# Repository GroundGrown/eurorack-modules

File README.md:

# eurorack-modules
All my older eurorack module designs

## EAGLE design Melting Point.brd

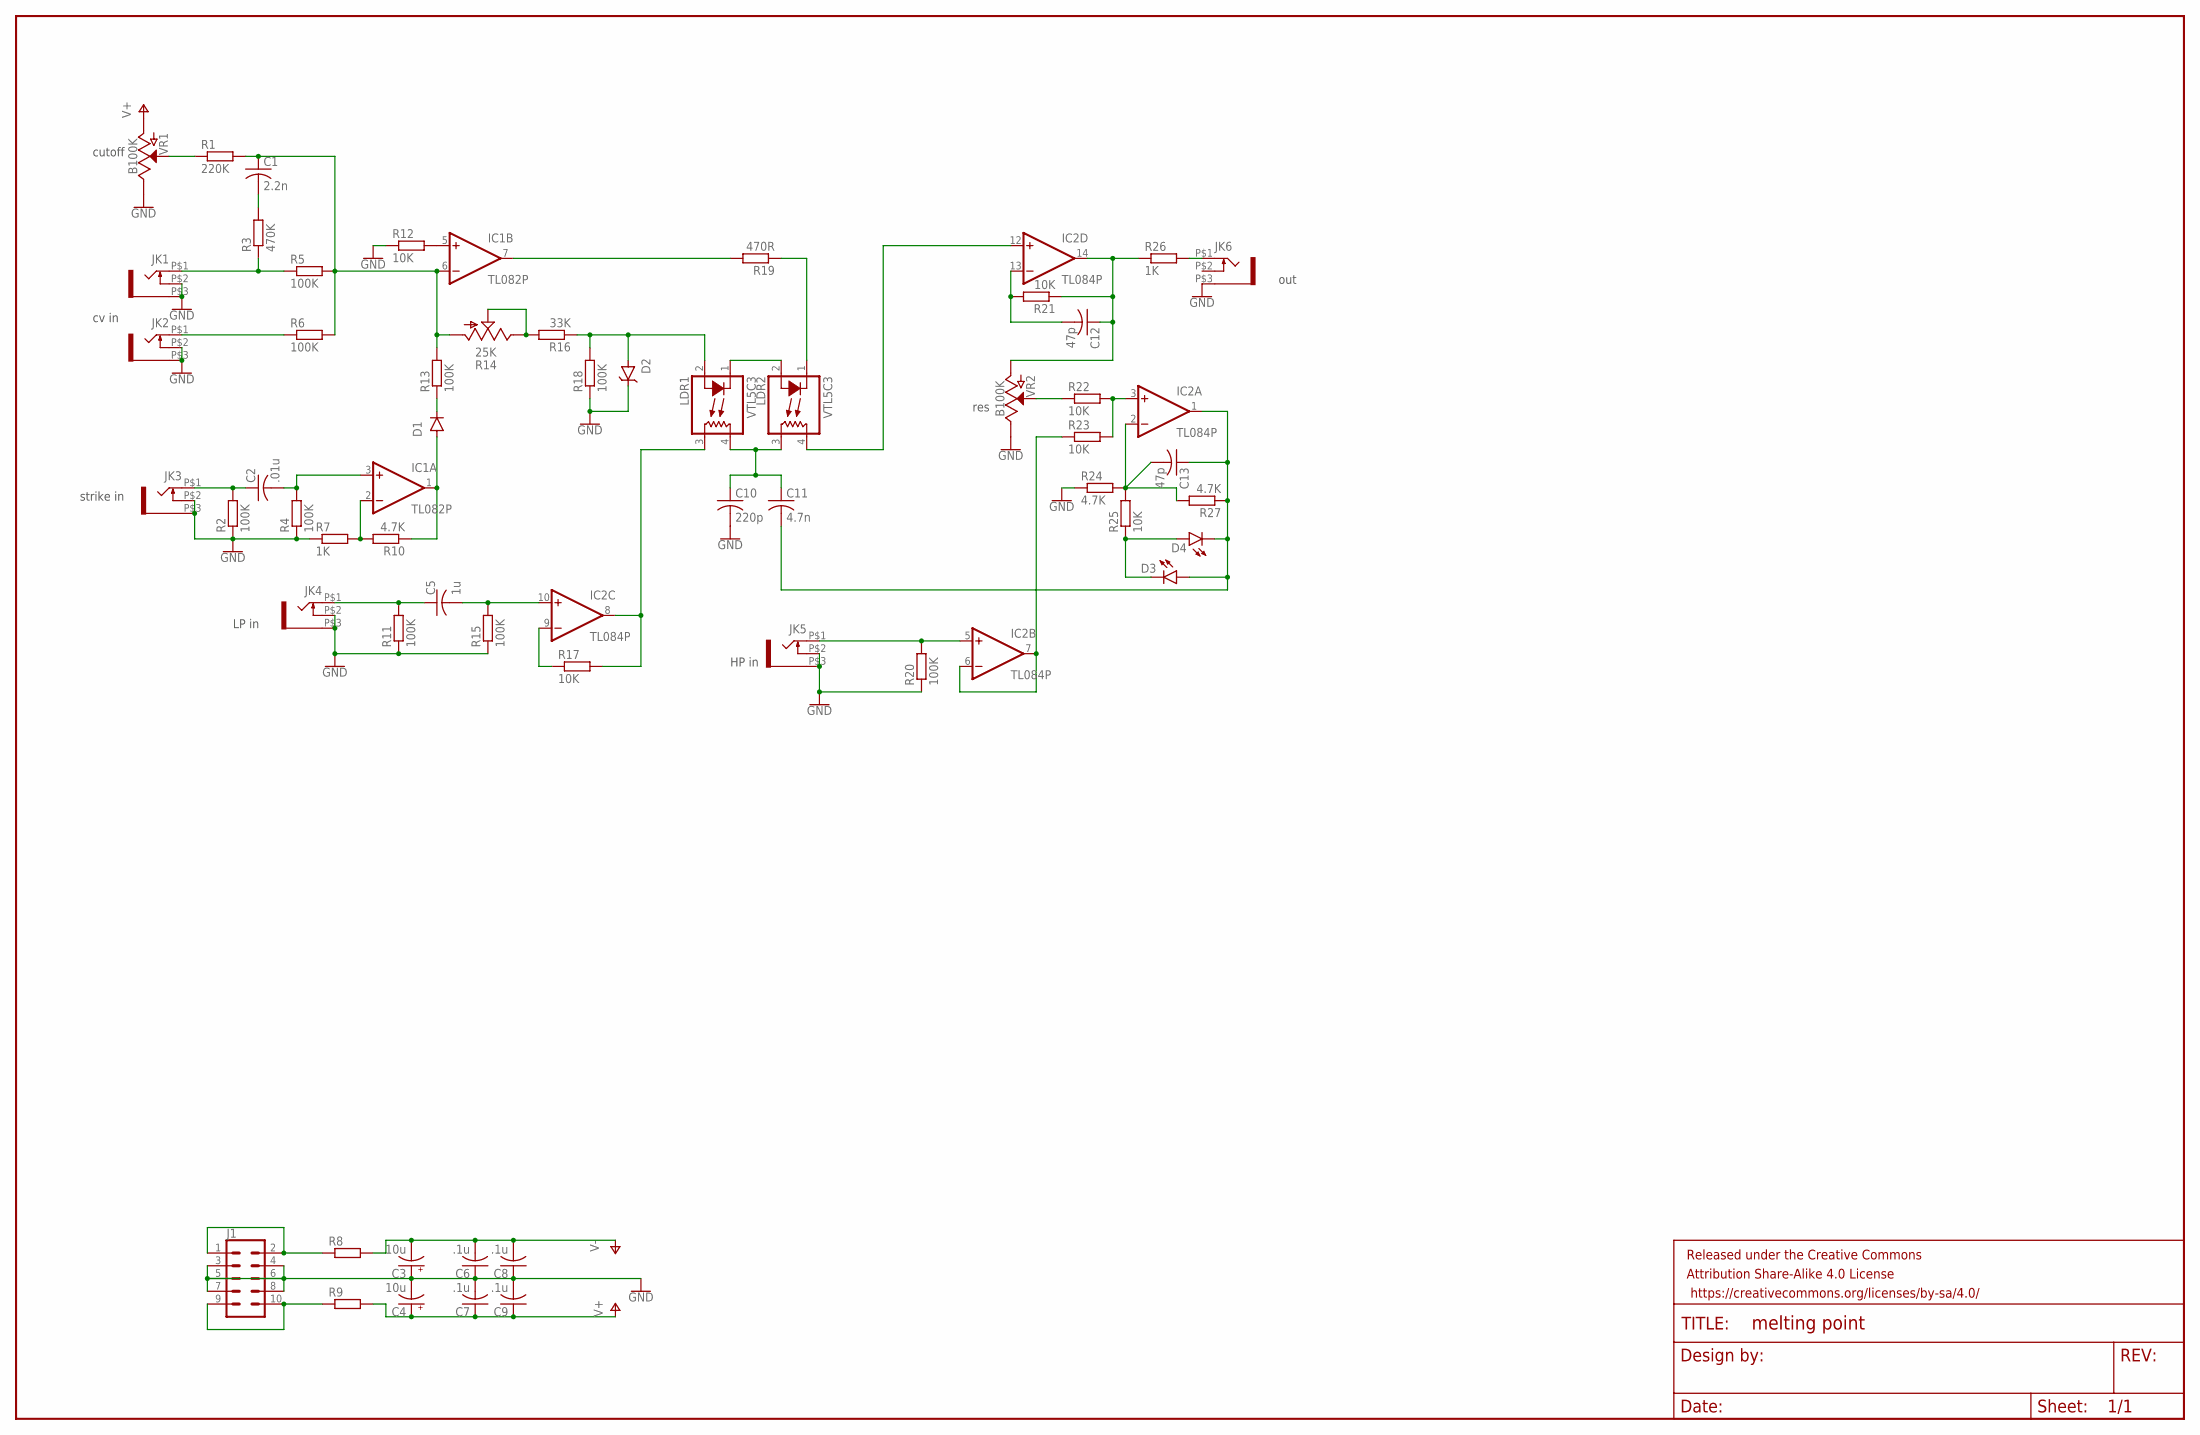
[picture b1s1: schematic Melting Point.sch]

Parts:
C1: 2.2n; C025-025X050
C2: .01u; C025-025X050
C3, C4: 10u; E2,5-6
C5: 1u; C050-045X075
C6, C7, C8, C9: .1u; C025-025X050
C10: 220p; C050-025X075
C11: 4.7n; C050-025X075
C12, C13: 47p; C025-025X050
D1: 1N4148DO35-7; DO35-7
D2: 1N4732A-TAP; DO-41
D3, D4: LED3MM; LED_3MM
FRAME1: FRAME-LEDGERNO_FOOTPRINT; DUMMY
IC1: TL082P; DIL08
IC2: TL084P; DIL14
J1: CONN_05X2PTH; 2X5
JK1, JK2, JK3, JK4, JK5, JK6: WQP-PJ301M-12_JACK
LDR1, LDR2: VTL5C3; VTL5C
R1: 220K; 0207/10
R2, R4, R5, R6, R11, R13, R15, R18, R20: 100K; 0207/10
R3: 470K; 0207/10
R7, R26: 1K; 0207/10
R8, R9: R-EU_0207/10; 0207/10
R10, R24, R27: 4.7K; 0207/10
R12, R17, R21, R22, R23, R25: 10K; 0207/10
R14: 25K; CA6V
R16: 33K; 0207/10
R19: 470R; 0207/10
VR1, VR2: B100K; POT-PTH-ALPS

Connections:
GND: C3.+, C4.-, C6.1, C7.2, C8.1, C9.2, C10.2, D2.C, J1.3, J1.4, J1.5, J1.6, J1.7, J1.8, JK1.P$2 (3), JK1.P$3 (1), JK2.P$2 (3), JK2.P$3 (1), JK3.P$2 (3), JK3.P$3 (1), JK4.P$2 (3), JK4.P$3 (1), JK5.P$2 (3), JK5.P$3 (1), JK6.P$3 (1), R2.1, R4.1, R7.1, R11.1, R12.1, R15.1, R18.1, R20.1, R24.1, VR1.P$1 (E), VR2.P$1 (E)
unnamed: J1.1, J1.2, R8.1
unnamed: J1.9, J1.10, R9.1
unnamed: D1.A, IC1.1 (OUT), R10.1
unnamed: JK2.P$1 (2), R6.1
unnamed: IC1.5 (+IN), R12.2
unnamed: C2.1, JK3.P$1 (2), R2.2
unnamed: C2.2, IC1.3 (+IN), R4.2
unnamed: C12.1, IC2.14 (OUT), R21.1, R26.1, VR2.P$3 (A)
unnamed: IC1.2 (-IN), R7.2, R10.2
unnamed: R22.1, VR2.P$2 (S)
unnamed: D1.C, R13.1
unnamed: IC2.5 (+IN), JK5.P$1 (2), R20.2
unnamed: IC2.6 (-IN), IC2.7 (OUT), R23.1
unnamed: C11.2, C13.1, D3.A, D4.K (C), IC2.1 (OUT), R27.1
unnamed: C1.1, IC1.6 (-IN), R1.2, R5.2, R6.2, R13.2, R14.A
unnamed: D3.K (C), D4.A, R25.1
unnamed: R14.E, R14.S, R16.2
unnamed: D2.A, LDR1.2 (A), R16.1, R18.2
unnamed: LDR1.1 (C), LDR2.2 (A)
unnamed: IC1.7 (OUT), R19.2
unnamed: LDR2.1 (C), R19.1
unnamed: C5.2, IC2.10 (+IN), R15.2
unnamed: IC2.9 (-IN), R17.1
unnamed: IC2.8 (OUT), LDR1.3 (L1), R17.2
unnamed: C10.1, C11.1, LDR1.4 (L2), LDR2.3 (L1)
unnamed: IC2.12 (+IN), LDR2.4 (L2)
unnamed: C12.2, IC2.13 (-IN), R21.2
unnamed: IC2.3 (+IN), R22.2, R23.2
unnamed: C13.2, IC2.2 (-IN), R24.2, R25.2, R27.2
unnamed: R1.1, VR1.P$2 (S)
unnamed: JK1.P$1 (2), R3.1, R5.1
unnamed: C1.2, R3.2
unnamed: C5.1, JK4.P$1 (2), R11.2
unnamed: JK6.P$1 (2), R26.2
V+: C4.+, C7.1, C9.1, IC1.8 (V+), IC2.4 (V+), R9.2, VR1.P$3 (A)
V-: C3.-, C6.2, C8.2, IC1.4 (V-), IC2.11 (V-), R8.2

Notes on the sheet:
cv in
strike in
LP in
HP in
out
cutoff
res

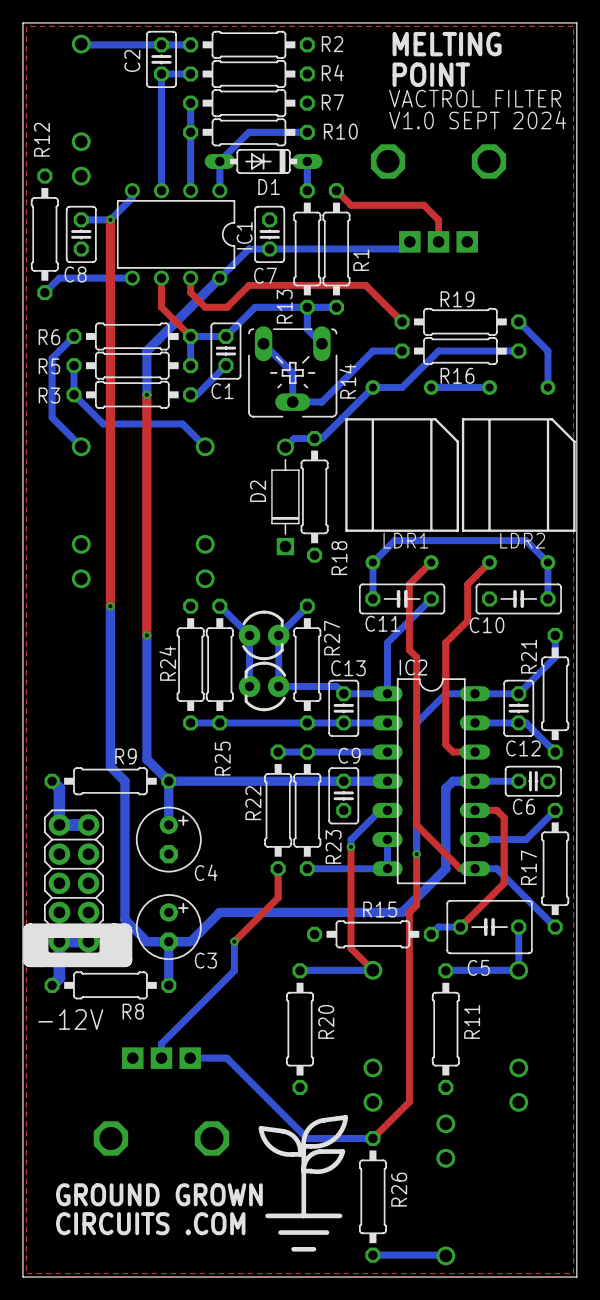
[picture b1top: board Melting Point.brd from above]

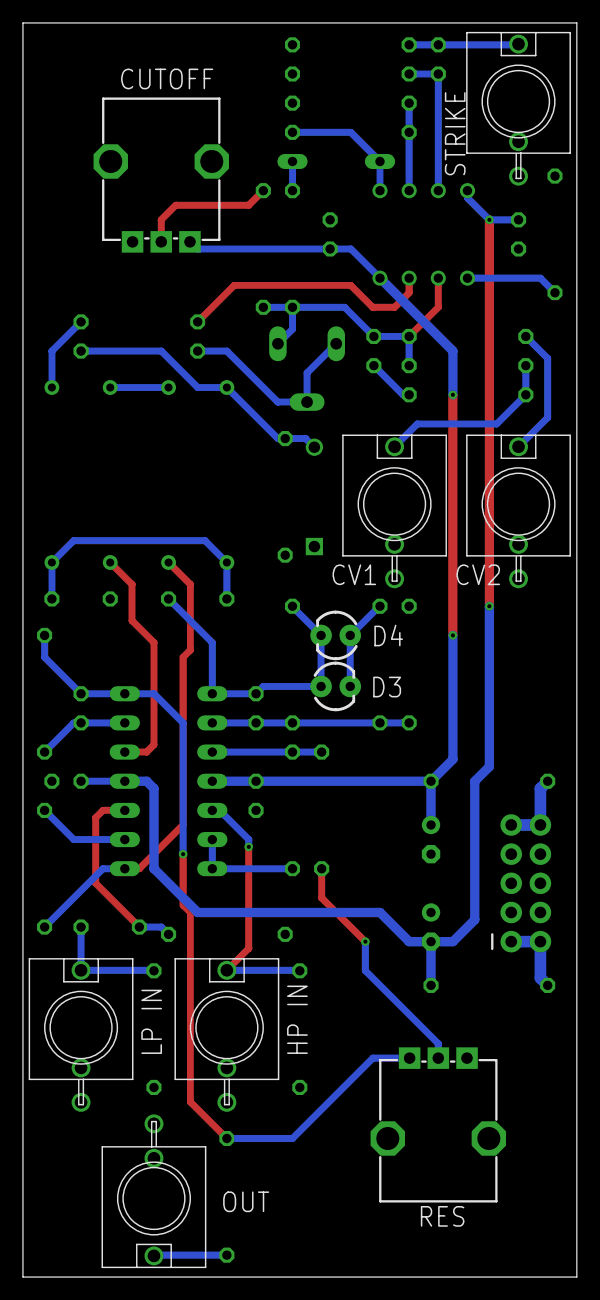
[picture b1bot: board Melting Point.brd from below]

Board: 2 copper layers, 48.2 x 109.2 mm, 59 parts (10 on the bottom side), 37 nets.

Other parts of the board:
U$1: LOGO_MED

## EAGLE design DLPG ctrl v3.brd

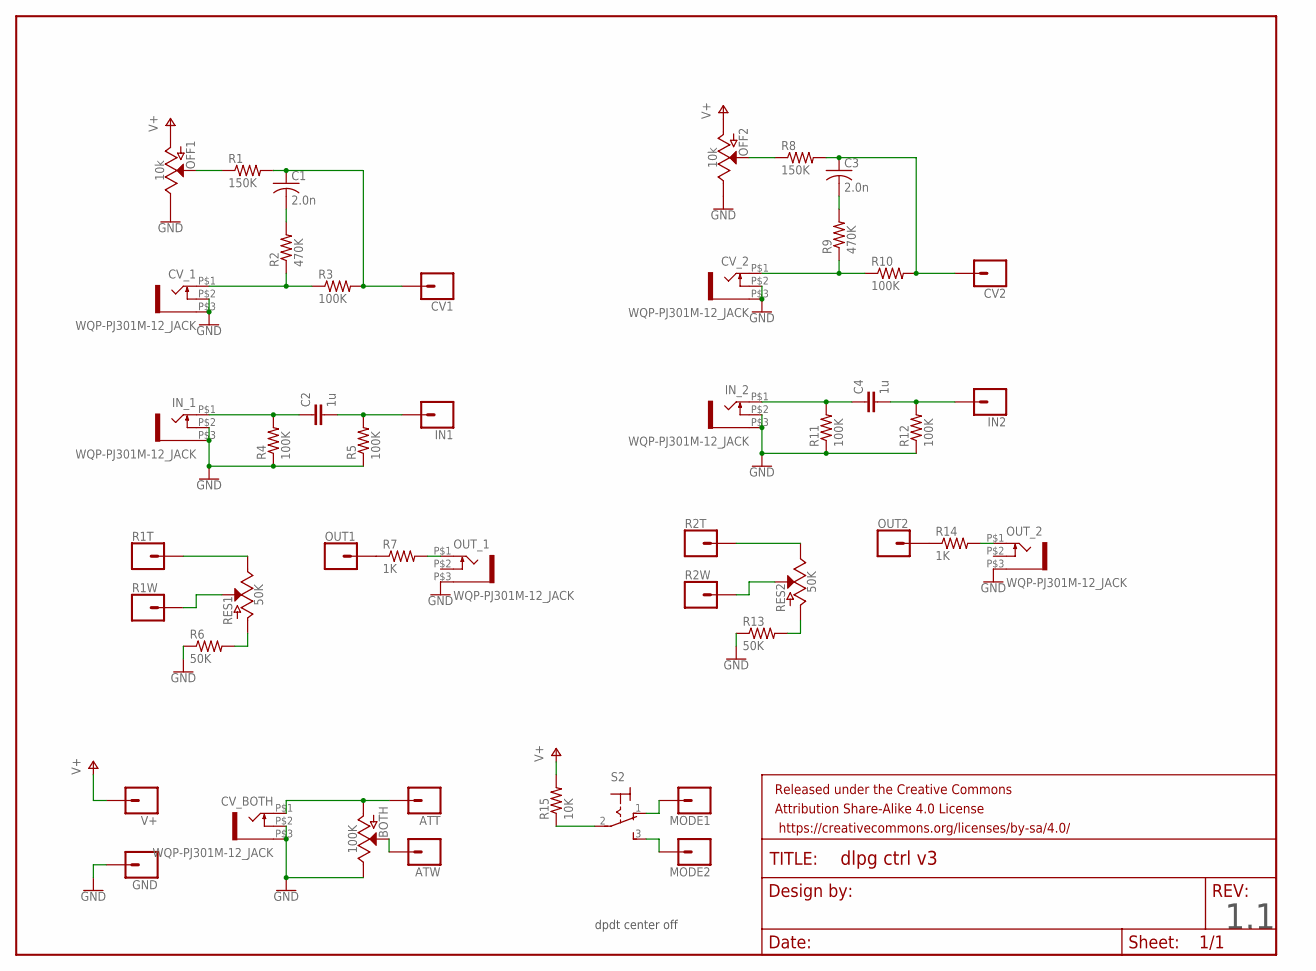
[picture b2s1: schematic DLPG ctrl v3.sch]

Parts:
ATT: CONN_01; 1X01
ATW: CONN_01; 1X01
BOTH: 100K; POT-PTH-ALPS
C1, C3: 2.0n; C0805K
C2, C4: 1u; C2220K
CV1, CV2: CONN_01; 1X01
CV_1, CV_2: WQP-PJ301M-12_JACK
CV_BOTH: WQP-PJ301M-12_JACK
FRAME1: FRAME-LETTERNO_PACKAGE; DUMMY
GND: CONN_01; 1X01
IN1, IN2: CONN_01; 1X01
IN_1, IN_2: WQP-PJ301M-12_JACK
MODE1, MODE2: CONN_01; 1X01
OFF1, OFF2: 10k; POT-PTH-ALPS
OUT1, OUT2: CONN_01; 1X01
OUT_1, OUT_2: WQP-PJ301M-12_JACK
R1, R8: 150K; M0805
R1T, R1W, R2T, R2W: CONN_01; 1X01
R2, R9: 470K; M0805
R3, R4, R5, R10, R11, R12: 100K; M0805
R6, R13: 50K; M0805
R7, R14: 1K; M0805
R15: 10K; M0805
RES1, RES2: 50K; POT-PTH-ALPS
S2: M9040P
V+: CONN_01; 1X01

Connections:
GND: BOTH.P$1 (E), CV_1.P$2 (3), CV_1.P$3 (1), CV_2.P$2 (3), CV_2.P$3 (1), CV_BOTH.P$2 (3), CV_BOTH.P$3 (1), GND.1, IN_1.P$2 (3), IN_1.P$3 (1), IN_2.P$2 (3), IN_2.P$3 (1), OFF1.P$1 (E), OFF2.P$1 (E), OUT_1.P$3 (1), OUT_2.P$3 (1), R4.1, R5.1, R6.1, R11.1, R12.1, R13.1
unnamed: OFF1.P$2 (S), R1.1
unnamed: C1.1, CV1.1, R1.2, R3.2
unnamed: CV_1.P$1 (2), R2.1, R3.1
unnamed: C1.2, R2.2
unnamed: C2.1, IN_1.P$1 (2), R4.2
unnamed: C2.2, IN1.1, R5.2
unnamed: OFF2.P$2 (S), R8.1
unnamed: R1T.1, RES1.P$1 (E)
unnamed: R1W.1, RES1.P$2 (S)
unnamed: R6.2, RES1.P$3 (A)
unnamed: OUT_1.P$1 (2), R7.2
unnamed: OUT1.1, R7.1
unnamed: C3.1, CV2.1, R8.2, R10.2
unnamed: CV_2.P$1 (2), R9.1, R10.1
unnamed: C3.2, R9.2
unnamed: C4.1, IN_2.P$1 (2), R11.2
unnamed: C4.2, IN2.1, R12.2
unnamed: R2T.1, RES2.P$1 (E)
unnamed: R2W.1, RES2.P$2 (S)
unnamed: R13.2, RES2.P$3 (A)
unnamed: OUT_2.P$1 (2), R14.2
unnamed: OUT2.1, R14.1
unnamed: R15.1, S2.2
unnamed: ATW.1, BOTH.P$2 (S)
unnamed: MODE2.1, S2.3 (S)
unnamed: MODE1.1, S2.1 (O)
unnamed: ATT.1, BOTH.P$3 (A), CV_BOTH.P$1 (2)
V+: OFF1.P$3 (A), OFF2.P$3 (A), R15.2, V+.1

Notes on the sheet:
dpdt center off
1.1

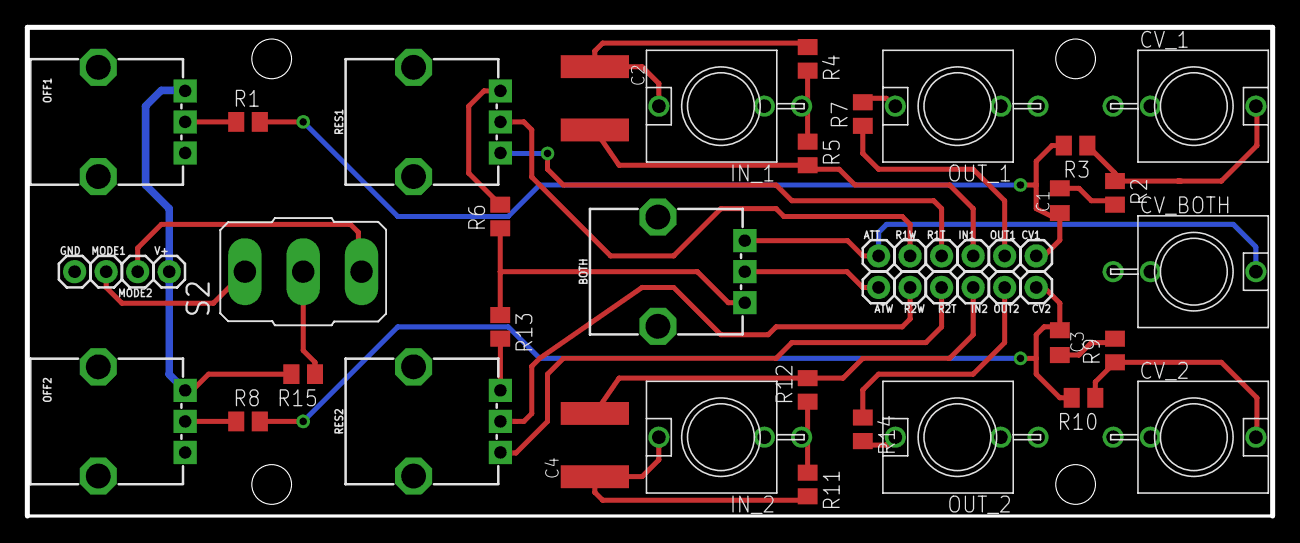
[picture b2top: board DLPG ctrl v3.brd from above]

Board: 2 copper layers, 100.3 x 39.4 mm, 49 parts (0 on the bottom side), 29 nets.

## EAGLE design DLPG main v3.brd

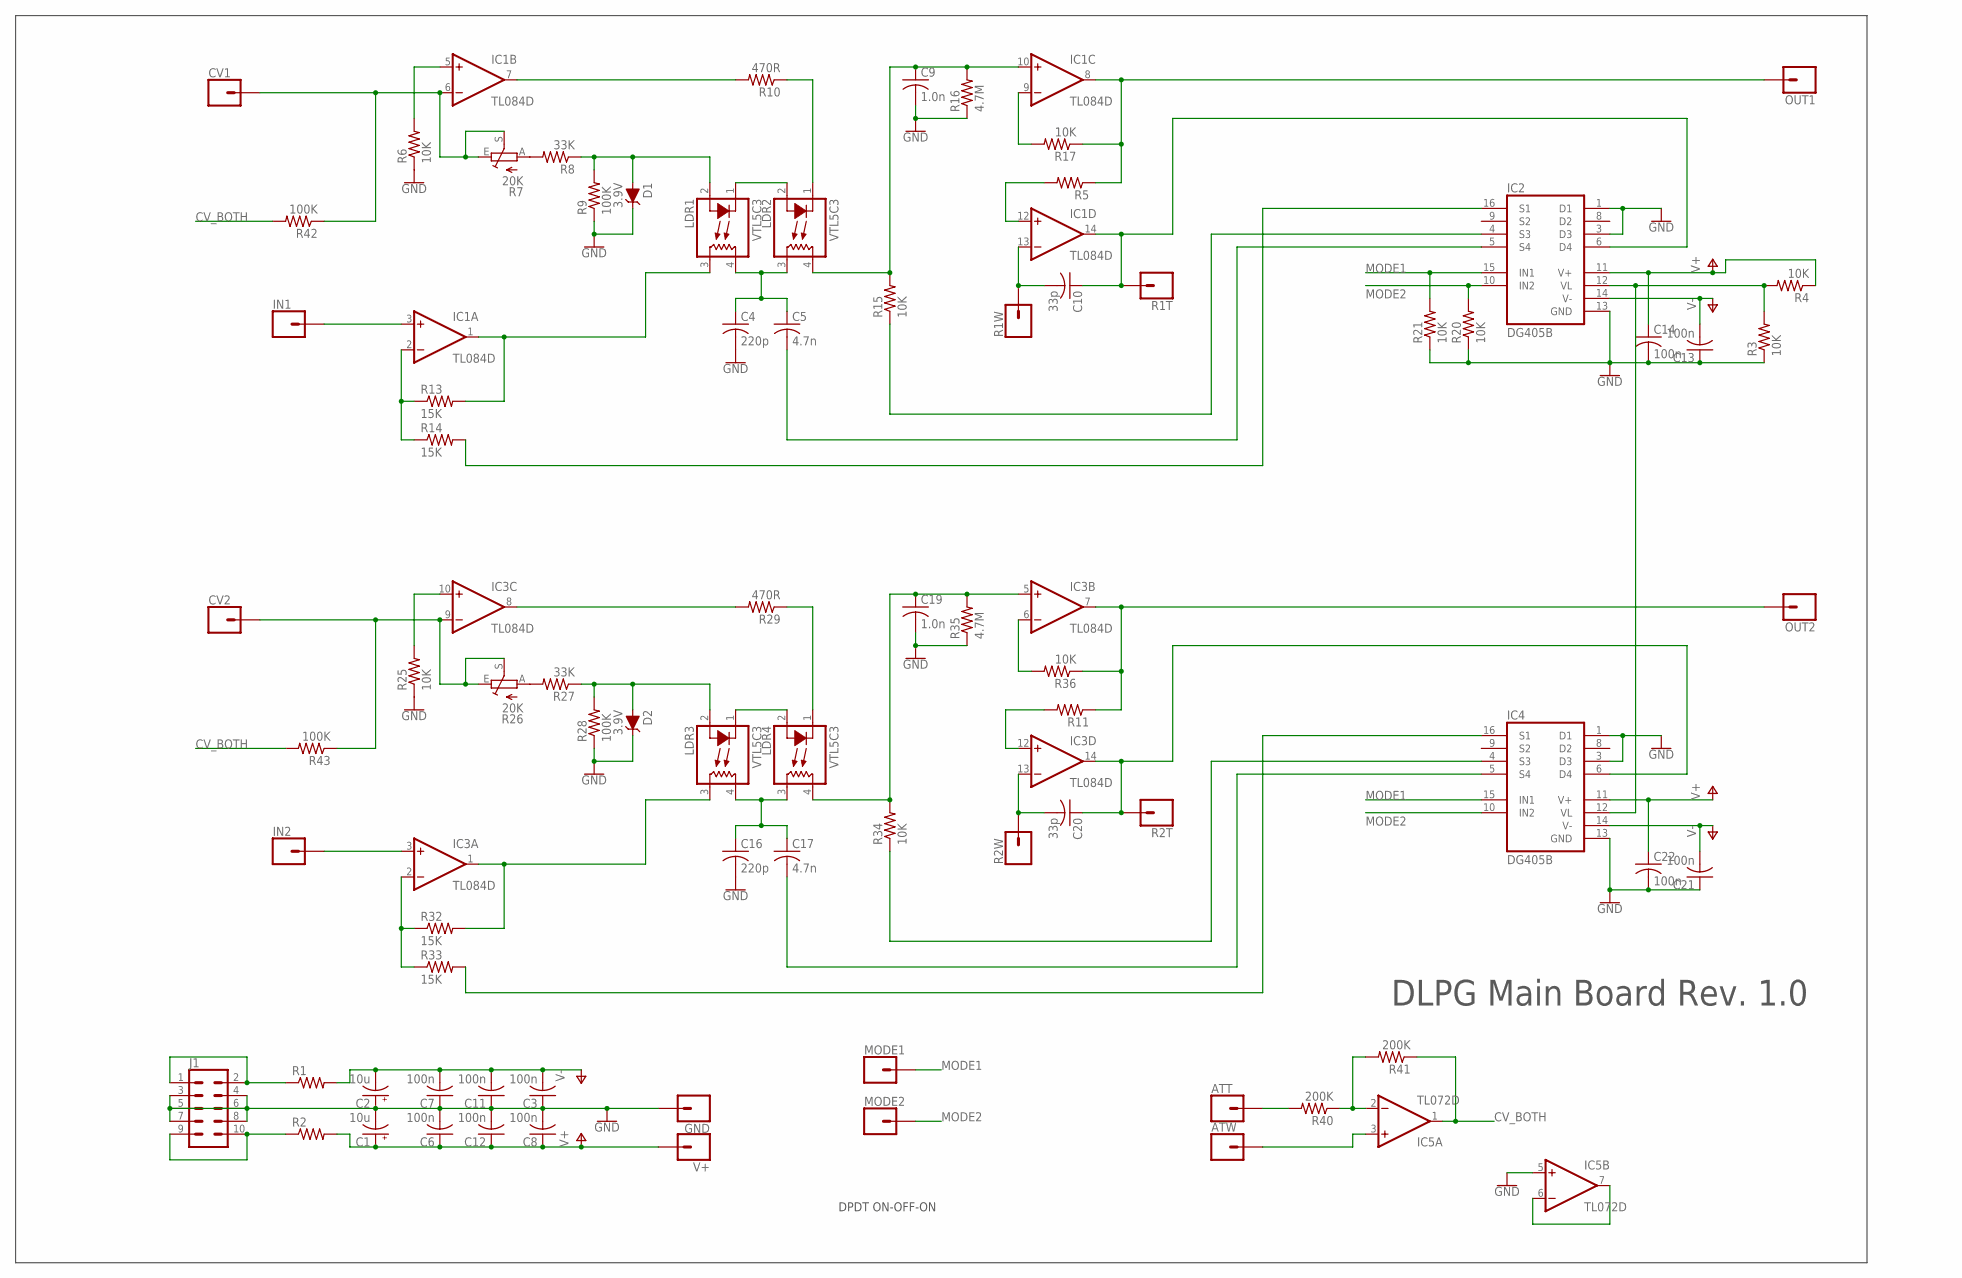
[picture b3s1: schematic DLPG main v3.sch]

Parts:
ATT: CONN_01; 1X01
ATW: CONN_01; 1X01
C1, C2: 10u; PANASONIC_C
C3, C6, C7, C8, C11, C12, C13, C14, C21, C22: 100n; C0805K
C4, C16: 220p; C0805K
C5, C17: 4.7n; C0805K
C9, C19: 1.0n; C0805K
C10, C20: 33p; C0805K
CV1, CV2: CONN_01; 1X01
D1, D2: 3.9V; SOD-323
GND: CONN_01; 1X01
IC1, IC3: TL084D; SO14
IC2, IC4: DG405B; SO16
IC5: TL072D; SO08
IN1, IN2: CONN_01; 1X01
J1: CONN_05X2PTH; 2X5
LDR1, LDR2, LDR3, LDR4: VTL5C3; VTL5C
MODE1, MODE2: CONN_01; 1X01
OUT1, OUT2: CONN_01; 1X01
R1, R2: RESISTOR0805-RES; 0805
R1T, R1W, R2T, R2W: CONN_01; 1X01
R3, R4, R6, R15, R17, R20, R21, R25, R34, R36: 10K; M0805
R5, R11: R-US_M0805; M0805
R7, R26: 20K; S64YW
R8, R27: 33K; M0805
R9, R28, R42, R43: 100K; M0805
R10, R29: 470R; M0805
R13, R14, R32, R33: 15K; M0805
R16, R35: 4.7M; M0805
R40, R41: 200K; M0805
V+: CONN_01; 1X01

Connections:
CV_BOTH: IC5.1 (OUT), R41.1, R42.2, R43.2
GND: C1.-, C2.+, C3.1, C4.2, C6.2, C7.1, C8.2, C9.2, C11.1, C12.2, C13.1, C14.2, C16.2, C19.2, C21.1, C22.2, D1.C, D2.C, GND.1, IC2.1 (D1), IC2.3 (D3), IC2.13 (GND), IC4.1 (D1), IC4.3 (D3), IC4.13 (GND), IC5.5 (+IN), J1.3, J1.4, J1.5, J1.6, J1.7, J1.8, R3.1, R6.1, R9.1, R16.1, R20.1, R21.1, R25.1, R28.1, R35.1
MODE1: IC2.15 (IN1), IC4.15 (IN1), MODE1.1, R21.2
MODE2: IC2.10 (IN2), IC4.10 (IN2), MODE2.1, R20.2
unnamed: J1.1, J1.2, R1.1
unnamed: J1.9, J1.10, R2.1
unnamed: IC1.7 (OUT), R10.2
unnamed: LDR2.1 (C), R10.1
unnamed: IC2.12 (VL), IC4.12 (VL), R3.2, R4.2
unnamed: IC1.3 (+IN), IN1.1
unnamed: IC1.2 (-IN), R13.1, R14.1
unnamed: IC1.12 (+IN), R5.2
unnamed: CV1.1, IC1.6 (-IN), R7.E, R7.S, R42.1
unnamed: IC3.12 (+IN), R11.2
unnamed: IC1.1 (OUT), LDR1.3 (L1), R13.2
unnamed: C4.1, C5.1, LDR1.4 (L2), LDR2.3 (L1)
unnamed: IC1.5 (+IN), R6.2
unnamed: R7.A, R8.2
unnamed: D1.A, LDR1.2 (A), R8.1, R9.2
unnamed: LDR1.1 (C), LDR2.2 (A)
unnamed: C9.1, IC1.10 (+IN), LDR2.4 (L2), R15.2, R16.2
unnamed: IC1.9 (-IN), R17.2
unnamed: IC1.8 (OUT), OUT1.1, R5.1, R17.1
unnamed: C10.2, IC1.13 (-IN), R1W.1
unnamed: IC2.4 (S3), R15.1
unnamed: C5.2, IC2.5 (S4)
unnamed: IC2.16 (S1), R14.2
unnamed: CV2.1, IC3.9 (-IN), R26.E, R26.S, R43.1
unnamed: IC3.10 (+IN), R25.2
unnamed: R26.A, R27.2
unnamed: D2.A, LDR3.2 (A), R27.1, R28.2
unnamed: LDR3.1 (C), LDR4.2 (A)
unnamed: IC3.8 (OUT), R29.2
unnamed: LDR4.1 (C), R29.1
unnamed: IC3.3 (+IN), IN2.1
unnamed: IC3.2 (-IN), R32.1, R33.1
unnamed: IC3.1 (OUT), LDR3.3 (L1), R32.2
unnamed: C16.1, C17.1, LDR3.4 (L2), LDR4.3 (L1)
unnamed: C19.1, IC3.5 (+IN), LDR4.4 (L2), R34.2, R35.2
unnamed: IC3.6 (-IN), R36.2
unnamed: IC3.7 (OUT), OUT2.1, R11.1, R36.1
unnamed: C20.1, IC3.14 (OUT), IC4.6 (D4), R2T.1
unnamed: C20.2, IC3.13 (-IN), R2W.1
unnamed: IC4.4 (S3), R34.1
unnamed: C17.2, IC4.5 (S4)
unnamed: IC4.16 (S1), R33.2
unnamed: ATT.1, R40.2
unnamed: ATW.1, IC5.3 (+IN)
unnamed: IC5.2 (-IN), R40.1, R41.2
unnamed: IC5.6 (-IN), IC5.7 (OUT)
unnamed: C10.1, IC1.14 (OUT), IC2.6 (D4), R1T.1
V+: C1.+, C6.1, C8.1, C12.1, C14.1, C22.1, IC1.4 (V+), IC2.11 (V+), IC3.4 (V+), IC4.11 (V+), IC5.8 (V+), R2.2, R4.1, V+.1
V-: C2.-, C3.2, C7.2, C11.2, C13.2, C21.2, IC1.11 (V-), IC2.14 (V-), IC3.11 (V-), IC4.14 (V-), IC5.4 (V-), R1.2

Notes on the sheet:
DPDT ON-OFF-ON
DLPG Main Board Rev. 1.0

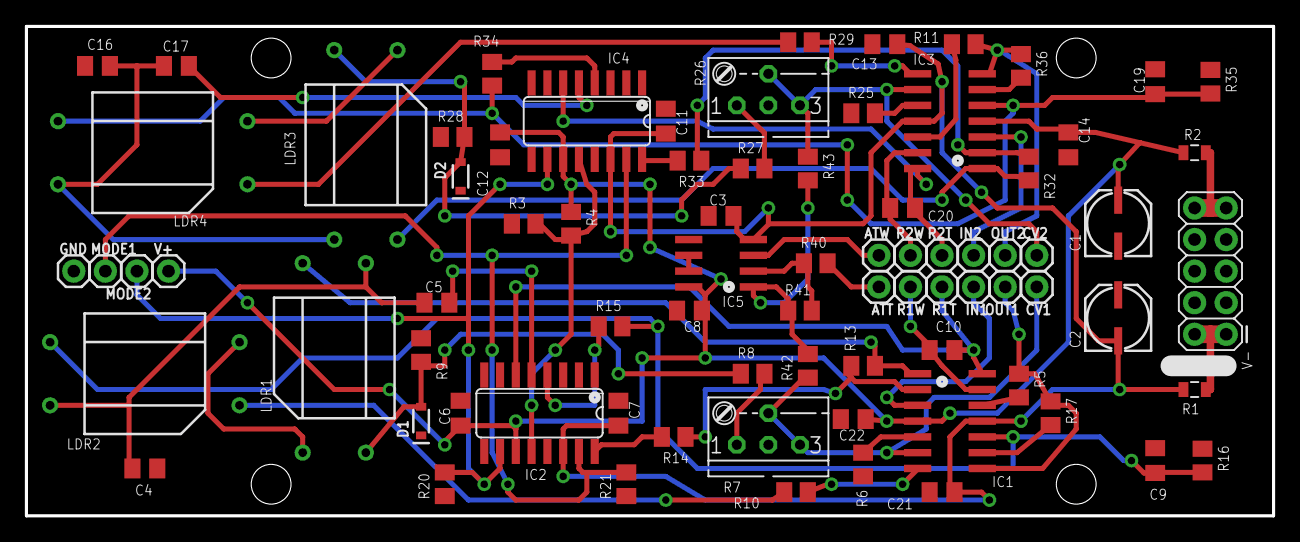
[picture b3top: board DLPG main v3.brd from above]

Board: 2 copper layers, 100.3 x 39.4 mm, 80 parts (0 on the bottom side), 53 nets.

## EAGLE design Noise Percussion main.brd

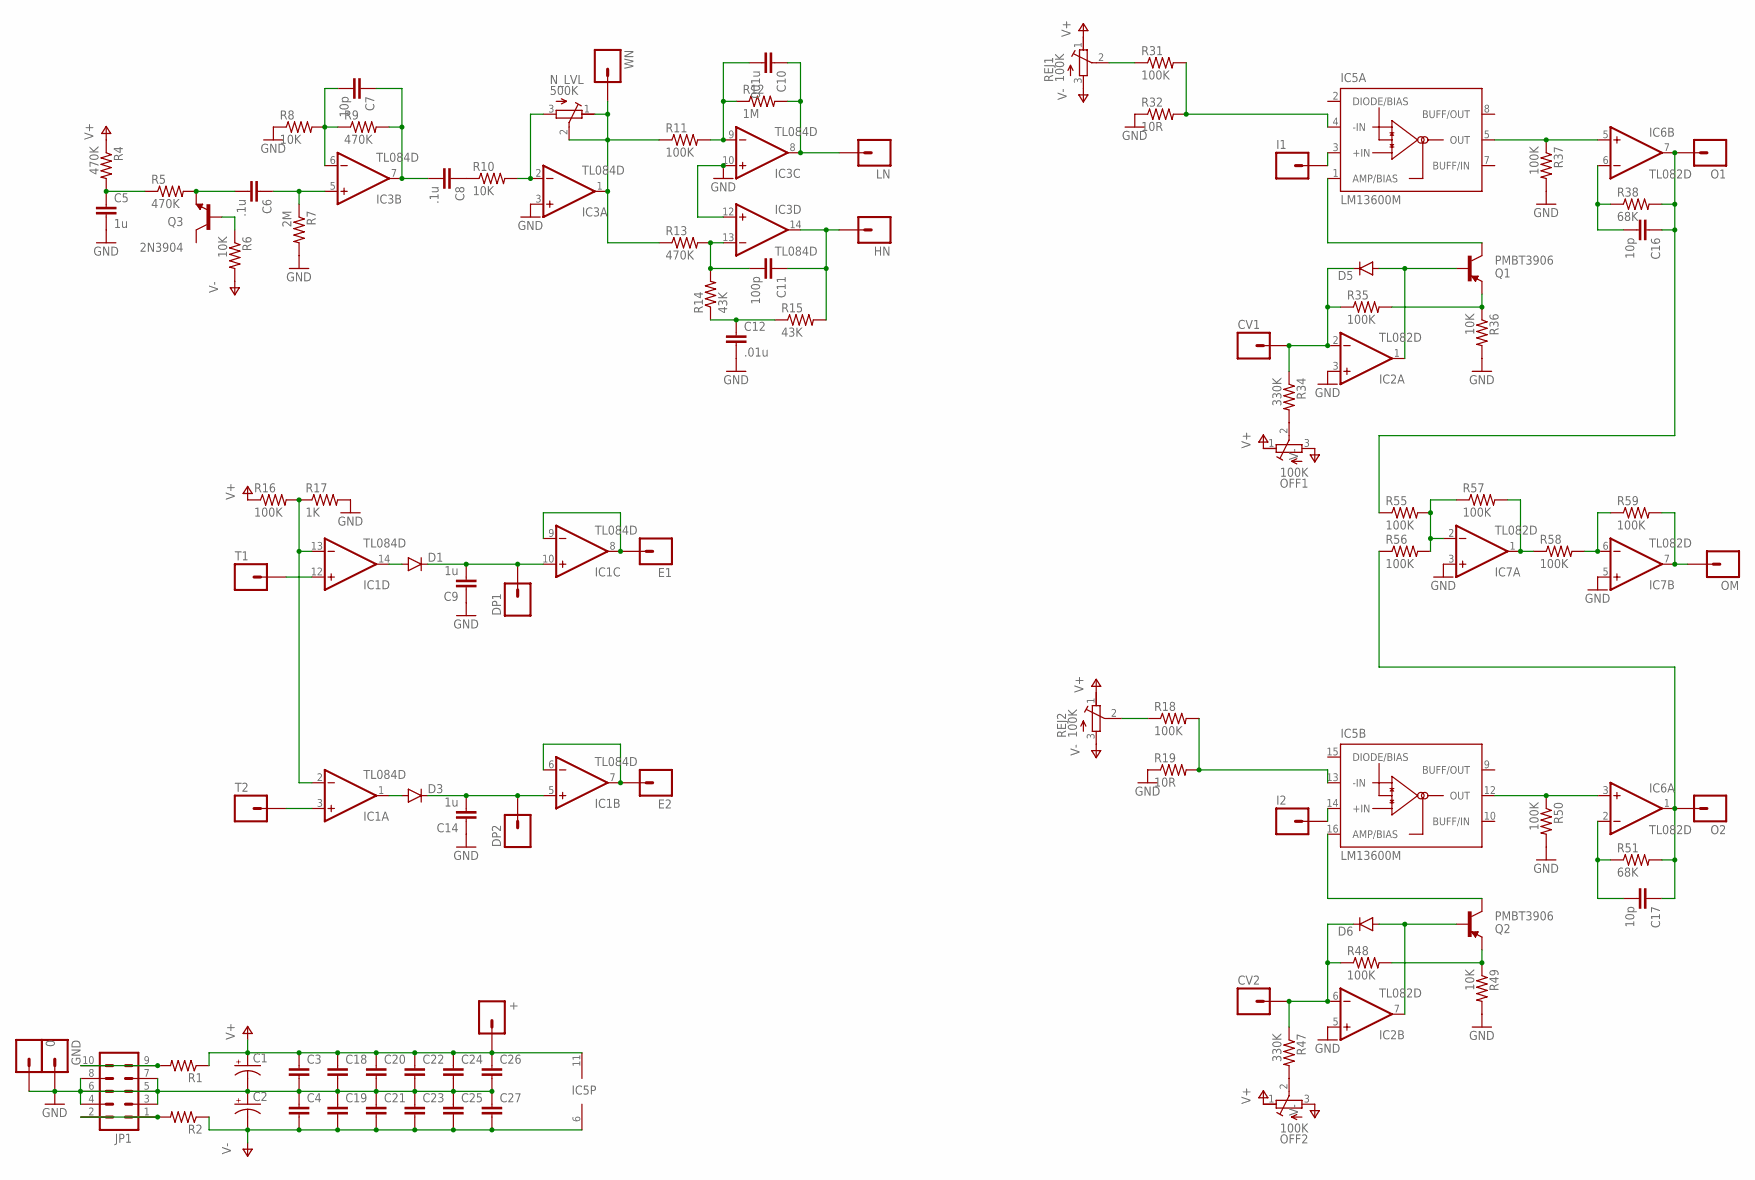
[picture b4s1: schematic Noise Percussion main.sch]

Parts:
0: M01PTH; 1X01
+: M01PTH; 1X01
C1, C2: CAP_POLC; PANASONIC_C
C3, C4, C18, C19, C20, C21, C22, C23, C24, C25, C26, C27: CAP0805; 0805
C5, C9, C14: 1u; 0805
C6, C8: .1u; 0805
C7, C16, C17: 10p; 0805
C10: .001u; 0805
C11: 100p; 0805
C12: .01u; 0805
CV1, CV2: M01PTH; 1X01
D1, D3, D5, D6: DIODESOD123; SOD-123
DP1, DP2: M01PTH; 1X01
E1, E2: M01PTH; 1X01
GND: M01PTH; 1X01
HN: M01PTH; 1X01
I1, I2: M01PTH; 1X01
IC1, IC3: TL084D; SO14
IC2, IC6, IC7: TL082D; SO08
IC5: LM13600M; SO16
JP1: M05X2PTH; AVR_ICSP
LN: M01PTH; 1X01
N_LVL: 500K; RTRIM3314G
O1, O2: M01PTH; 1X01
OFF1, OFF2: 100K; RTRIM3314G
OM: M01PTH; 1X01
Q1, Q2: PMBT3906; SOT23-3
Q3: 2N3904; TO92
R1, R2: RESISTOR0805-RES; 0805
R4, R5, R9, R13: 470K; 0805
R6, R8, R10, R36, R49: 10K; 0805
R7: 2M; 0805
R11, R16, R18, R31, R35, R37, R48, R50, R55, R56, R57, R58, R59: 100K; 0805
R12: 1M; 0805
R14, R15: 43K; 0805
R17: 1K; 0805
R19, R32: 10R; 0805
R34, R47: 330K; 0805
R38, R51: 68K; 0805
REJ1, REJ2: 100K; RTRIM3314G
T1, T2: M01PTH; 1X01
WN: M01PTH; 1X01

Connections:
GND: 0.1, C1.-, C2.+, C3.2, C4.1, C5.2, C9.1, C12.2, C14.1, C18.2, C19.1, C20.2, C21.1, C22.2, C23.1, C24.2, C25.1, C26.2, C27.1, GND.1, IC2.3 (+IN), IC2.5 (+IN), IC3.3 (+IN), IC3.10 (+IN), IC3.12 (+IN), IC7.3 (+IN), IC7.5 (+IN), JP1.3, JP1.4, JP1.5, JP1.6, JP1.7, JP1.8, R7.2, R8.1, R17.2, R19.1, R32.1, R36.2, R37.2, R49.2, R50.2
unnamed: JP1.9, JP1.10, R1.2
unnamed: JP1.1, JP1.2, R2.2
unnamed: I1.1, IC5.3 (+IN)
unnamed: C5.1, R4.2, R5.1
unnamed: C6.2, Q3.3 (E), R5.2
unnamed: C6.1, IC3.5 (+IN), R7.1
unnamed: Q3.2 (B), R6.1
unnamed: C7.2, IC3.6 (-IN), R8.2, R9.1
unnamed: C7.1, C8.2, IC3.7 (OUT), R9.2
unnamed: C8.1, R10.1
unnamed: IC3.2 (-IN), N_LVL.3 (A), R10.2
unnamed: IC3.1 (OUT), N_LVL.1 (E), N_LVL.2 (S), R11.1, R13.1, WN.1
unnamed: C10.2, IC3.9 (-IN), R11.2, R12.1
unnamed: C10.1, IC3.8 (OUT), LN.1, R12.2
unnamed: C11.2, IC3.13 (-IN), R13.2, R14.2
unnamed: C12.1, R14.1, R15.1
unnamed: C11.1, HN.1, IC3.14 (OUT), R15.2
unnamed: IC1.3 (+IN), T2.1
unnamed: IC1.12 (+IN), T1.1
unnamed: D1.A, IC1.14 (OUT)
unnamed: C9.2, D1.C, DP1.1, IC1.10 (+IN)
unnamed: E1.1, IC1.8 (OUT), IC1.9 (-IN)
unnamed: I2.1, IC5.14 (+IN)
unnamed: R18.1, REJ2.2 (S)
unnamed: IC5.13 (-IN), R18.2, R19.2
unnamed: IC1.2 (-IN), IC1.13 (-IN), R16.2, R17.1
unnamed: D3.A, IC1.1 (OUT)
unnamed: C14.2, D3.C, DP2.1, IC1.5 (+IN)
unnamed: E2.1, IC1.6 (-IN), IC1.7 (OUT)
unnamed: R31.1, REJ1.2 (S)
unnamed: IC5.4 (-IN), R31.2, R32.2
unnamed: OFF1.2 (S), R34.2
unnamed: CV1.1, D5.C, IC2.2 (-IN), R34.1, R35.1
unnamed: Q1.2 (E), R35.2, R36.1
unnamed: D5.A, IC2.1 (OUT), Q1.1 (B)
unnamed: IC5.1 (AMP/BIAS), Q1.3 (C)
unnamed: IC5.5 (OUT), IC6.5 (+IN), R37.1
unnamed: C16.2, IC6.6 (-IN), R38.1
unnamed: C16.1, IC6.7 (OUT), O1.1, R38.2, R55.1
unnamed: OFF2.2 (S), R47.2
unnamed: CV2.1, D6.C, IC2.6 (-IN), R47.1, R48.1
unnamed: Q2.2 (E), R48.2, R49.1
unnamed: D6.A, IC2.7 (OUT), Q2.1 (B)
unnamed: IC5.16 (AMP/BIAS), Q2.3 (C)
unnamed: IC5.12 (OUT), IC6.3 (+IN), R50.1
unnamed: C17.2, IC6.2 (-IN), R51.1
unnamed: C17.1, IC6.1 (OUT), O2.1, R51.2, R56.1
unnamed: IC7.2 (-IN), R55.2, R56.2, R57.1
unnamed: IC7.1 (OUT), R57.2, R58.1
unnamed: IC7.6 (-IN), R58.2, R59.1
unnamed: IC7.7 (OUT), OM.1, R59.2
V+: +.1, C1.+, C3.1, C18.1, C20.1, C22.1, C24.1, C26.1, IC1.4 (V+), IC2.8 (V+), IC3.4 (V+), IC5.11 (V+), IC6.8 (V+), IC7.8 (V+), OFF1.1 (E), OFF2.1 (E), R1.1, R4.1, R16.1, REJ1.1 (E), REJ2.1 (E)
V-: C2.-, C4.2, C19.2, C21.2, C23.2, C25.2, C27.2, IC1.11 (V-), IC2.4 (V-), IC3.11 (V-), IC5.6 (V-), IC6.4 (V-), IC7.4 (V-), OFF1.3 (A), OFF2.3 (A), R2.1, R6.2, REJ1.3 (A), REJ2.3 (A)

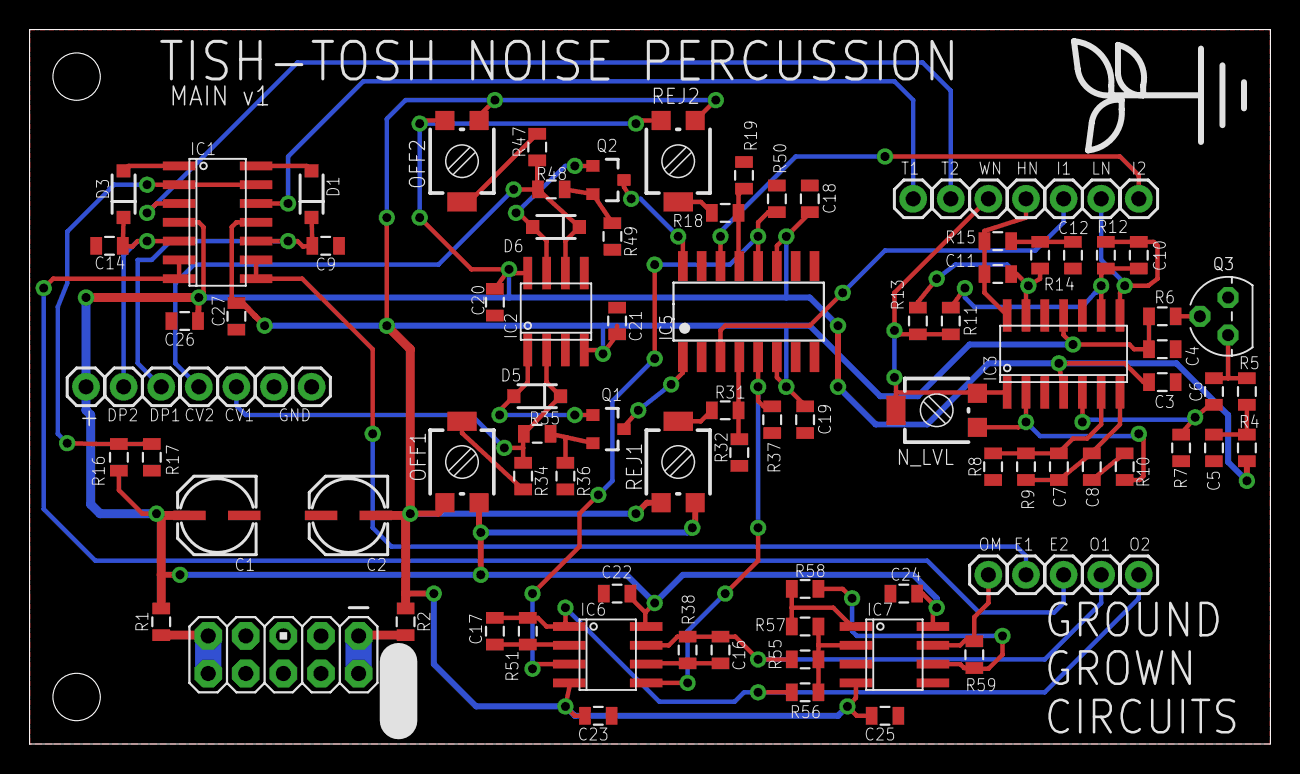
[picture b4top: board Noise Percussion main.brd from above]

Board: 2 copper layers, 83.8 x 48.3 mm, 99 parts (0 on the bottom side), 54 nets.

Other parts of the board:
U$1: LOGO_MED

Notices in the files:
parts and their libraries:
SparkFun-Connectors: Licensing: Creative Commons ShareAlike 4.0 International - https://creativecommons.org/licenses/by-sa/4.0
SparkFun-Aesthetics: Released under the Creative Commons Attribution Share-Alike 4.0 License
SparkFun-Aesthetics: https://creativecommons.org/licenses/by-sa/4.0
